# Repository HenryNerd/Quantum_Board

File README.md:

# Quantum Board #
A nice 65% or 95%ish keyboard. It using kailh chocs for great performance while being very small.

## Layout 

## Board Screenshots

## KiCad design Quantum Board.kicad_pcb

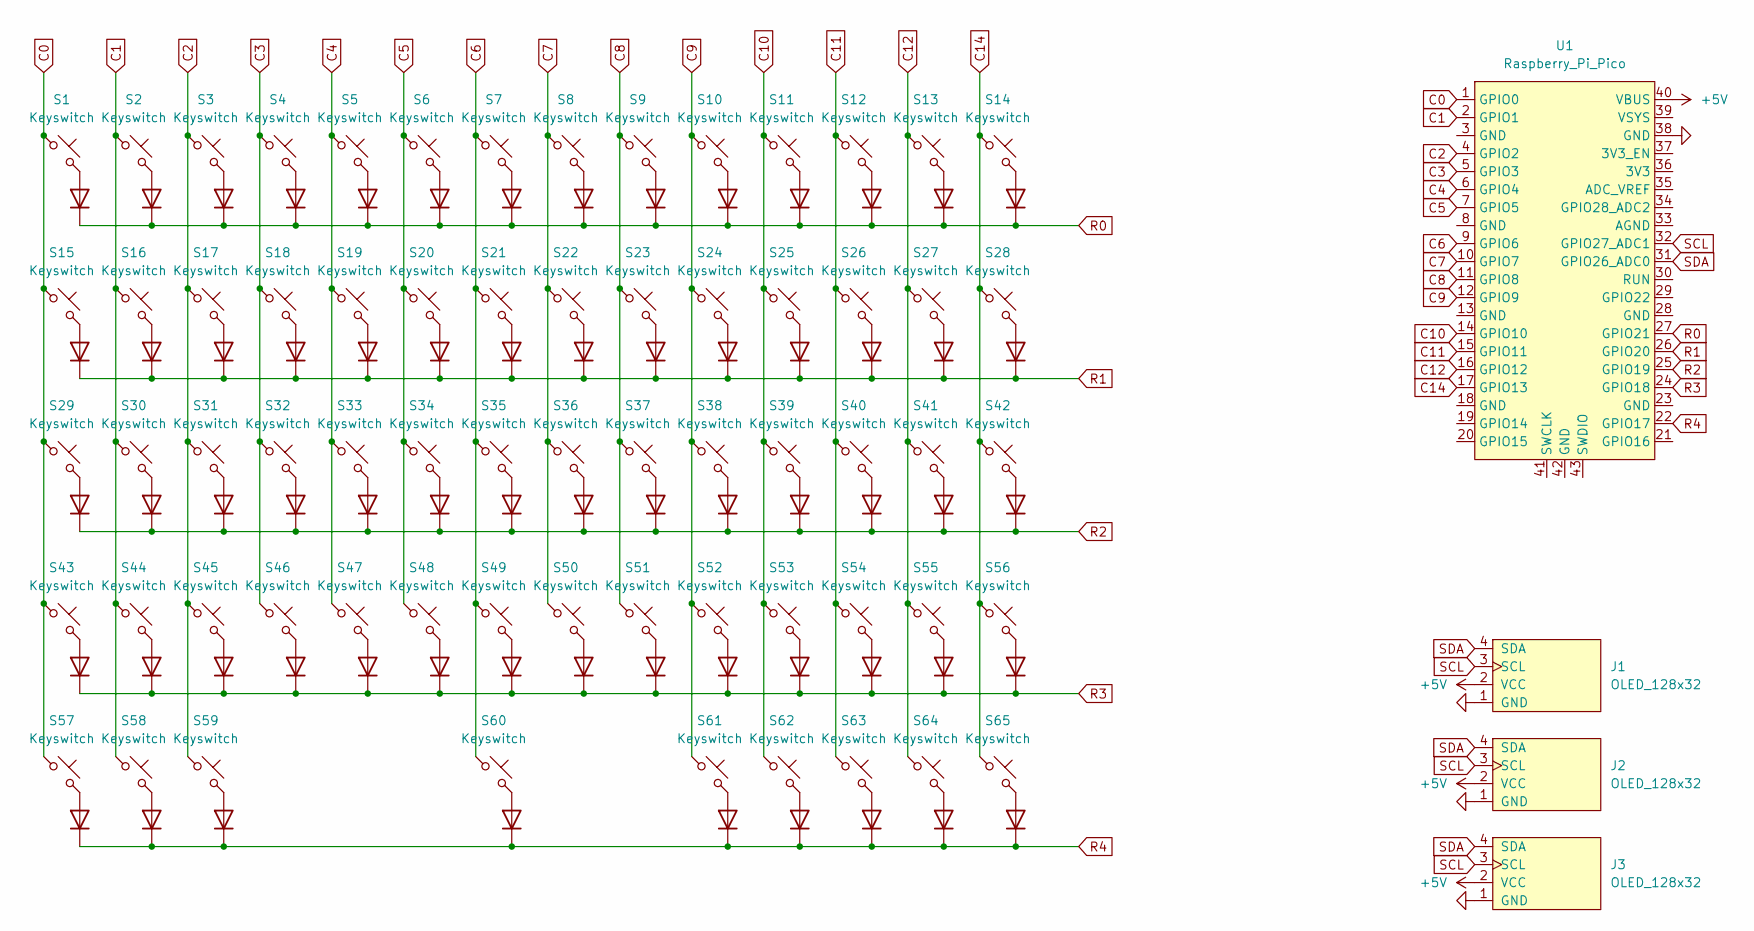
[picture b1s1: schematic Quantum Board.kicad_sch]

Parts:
D1, D2, D3, D4, D5, D6, D7, D8, D9, D10, D11, D12, D13, D14, D15, D16, D17, D18, D19, D20, D21, D22, D23, D24, D25, D26, D27, D28, D29, D30, D31, D32, D33, D34, D35, D36, D37, D38, D39, D40, D41, D42, D43, D44, D45, D46, D47, D48, D49, D50, D51, D52, D53, D54, D55, D56, D57, D58, D59, D60, D61, D62, D63, D64, D65: Diode; Diode_DO-35
J1, J2, J3: OLED_128x32
S1, S14, S15, S28, S29, S42, S43, S56, S57, S58, S59, S62: Keyswitch; Choc_V1_1.50u
S2, S3, S4, S5, S6, S7, S8, S9, S10, S11, S12, S13, S16, S17, S18, S19, S20, S21, S22, S23, S24, S25, S26, S27, S30, S31, S32, S33, S34, S35, S36, S37, S38, S39, S40, S41, S44, S45, S46, S47, S48, S49, S50, S51, S52, S53, S54, S55, S61, S63, S64, S65: Keyswitch; Choc_V1_1.00u
S60: Keyswitch; Choc_V1_5.50u
U1: Raspberry_Pi_Pico

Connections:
+5V: J1.2 (VCC), J2.2 (VCC), J3.2 (VCC), U1.40 (VBUS)
C0: S1.1, S15.1, S29.1, S43.1, S57.1, U1.1 (GPIO0)
C1: S2.1, S16.1, S30.1, S44.1, S58.1, U1.2 (GPIO1)
C2: S3.1, S17.1, S31.1, S45.1, S59.1, U1.4 (GPIO2)
C3: S4.1, S18.1, S32.1, S46.1, U1.5 (GPIO3)
C4: S5.1, S19.1, S33.1, S47.1, U1.6 (GPIO4)
C5: S6.1, S20.1, S34.1, S48.1, U1.7 (GPIO5)
C6: S7.1, S21.1, S35.1, S49.1, S60.1, U1.9 (GPIO6)
C7: S8.1, S22.1, S36.1, S50.1, U1.10 (GPIO7)
C8: S9.1, S23.1, S37.1, S51.1, U1.11 (GPIO8)
C9: S10.1, S24.1, S38.1, S52.1, S61.1, U1.12 (GPIO9); also elsewhere on the board
C10: S11.1, S25.1, S39.1, S53.1, S62.1, U1.14 (GPIO10); also elsewhere on the board
C11: S12.1, S26.1, S40.1, S54.1, S63.1, U1.15 (GPIO11); also elsewhere on the board
C12: S13.1, S27.1, S41.1, S55.1, S64.1, U1.16 (GPIO12); also elsewhere on the board
C14: S14.1, S28.1, S42.1, S56.1, S65.1, U1.17 (GPIO13); also elsewhere on the board
GND: J1.1 (GND), J2.1 (GND), J3.1 (GND), U1.38 (GND)
unnamed: D1.2 (A), S1.2
unnamed: D2.2 (A), S2.2
unnamed: D3.2 (A), S3.2
unnamed: D4.2 (A), S4.2
unnamed: D5.2 (A), S5.2
unnamed: D6.2 (A), S6.2
unnamed: D7.2 (A), S7.2
unnamed: D8.2 (A), S8.2
unnamed: D9.2 (A), S9.2
unnamed: D10.2 (A), S10.2
unnamed: D11.2 (A), S11.2
unnamed: D12.2 (A), S12.2
unnamed: D13.2 (A), S13.2
unnamed: D14.2 (A), S14.2
unnamed: D15.2 (A), S15.2
unnamed: D16.2 (A), S16.2
unnamed: D17.2 (A), S17.2
unnamed: D18.2 (A), S18.2
unnamed: D19.2 (A), S19.2
unnamed: D20.2 (A), S20.2
unnamed: D21.2 (A), S21.2
unnamed: D22.2 (A), S22.2
unnamed: D23.2 (A), S23.2
unnamed: D24.2 (A), S24.2
unnamed: D25.2 (A), S25.2
unnamed: D26.2 (A), S26.2
unnamed: D27.2 (A), S27.2
unnamed: D28.2 (A), S28.2
unnamed: D29.2 (A), S29.2
unnamed: D30.2 (A), S30.2
unnamed: D31.2 (A), S31.2
unnamed: D32.2 (A), S32.2
unnamed: D33.2 (A), S33.2
unnamed: D34.2 (A), S34.2
unnamed: D35.2 (A), S35.2
unnamed: D36.2 (A), S36.2
unnamed: D37.2 (A), S37.2
unnamed: D38.2 (A), S38.2
unnamed: D39.2 (A), S39.2
unnamed: D40.2 (A), S40.2
unnamed: D41.2 (A), S41.2
unnamed: D42.2 (A), S42.2
unnamed: D43.2 (A), S43.2
unnamed: D44.2 (A), S44.2
unnamed: D45.2 (A), S45.2
unnamed: D46.2 (A), S46.2
unnamed: D47.2 (A), S47.2
unnamed: D48.2 (A), S48.2
unnamed: D49.2 (A), S49.2
unnamed: D50.2 (A), S50.2
unnamed: D51.2 (A), S51.2
unnamed: D52.2 (A), S52.2
unnamed: D53.2 (A), S53.2
unnamed: D54.2 (A), S54.2
unnamed: D55.2 (A), S55.2
unnamed: D56.2 (A), S56.2
unnamed: D57.2 (A), S57.2
unnamed: D58.2 (A), S58.2
unnamed: D59.2 (A), S59.2
unnamed 75: D60.2 (A), S61.2; also elsewhere on the board
unnamed: D61.2 (A), S62.2
unnamed: D62.2 (A), S63.2
unnamed: D63.2 (A), S60.2
unnamed: D64.2 (A), S64.2
unnamed: D65.2 (A), S65.2
R0: D1.1 (K), D2.1 (K), D3.1 (K), D4.1 (K), D5.1 (K), D6.1 (K), D7.1 (K), D8.1 (K), D9.1 (K), D10.1 (K), D11.1 (K), D12.1 (K), D13.1 (K), D14.1 (K), U1.27 (GPIO21)
R1: D15.1 (K), D16.1 (K), D17.1 (K), D18.1 (K), D19.1 (K), D20.1 (K), D21.1 (K), D22.1 (K), D23.1 (K), D24.1 (K), D25.1 (K), D26.1 (K), D27.1 (K), D28.1 (K), U1.26 (GPIO20)
R2: D29.1 (K), D30.1 (K), D31.1 (K), D32.1 (K), D33.1 (K), D34.1 (K), D35.1 (K), D36.1 (K), D37.1 (K), D38.1 (K), D39.1 (K), D40.1 (K), D41.1 (K), D42.1 (K), U1.25 (GPIO19)
R3: D43.1 (K), D44.1 (K), D45.1 (K), D46.1 (K), D47.1 (K), D48.1 (K), D49.1 (K), D50.1 (K), D51.1 (K), D52.1 (K), D53.1 (K), D54.1 (K), D55.1 (K), D56.1 (K), U1.24 (GPIO18)
R4: D57.1 (K), D58.1 (K), D59.1 (K), D60.1 (K), D61.1 (K), D62.1 (K), D63.1 (K), D64.1 (K), D65.1 (K), U1.22 (GPIO17); also elsewhere on the board
SCL: J1.3 (SCL), J2.3 (SCL), J3.3 (SCL), U1.32 (GPIO27_ADC1)
SDA: J1.4 (SDA), J2.4 (SDA), J3.4 (SDA), U1.31 (GPIO26_ADC0)

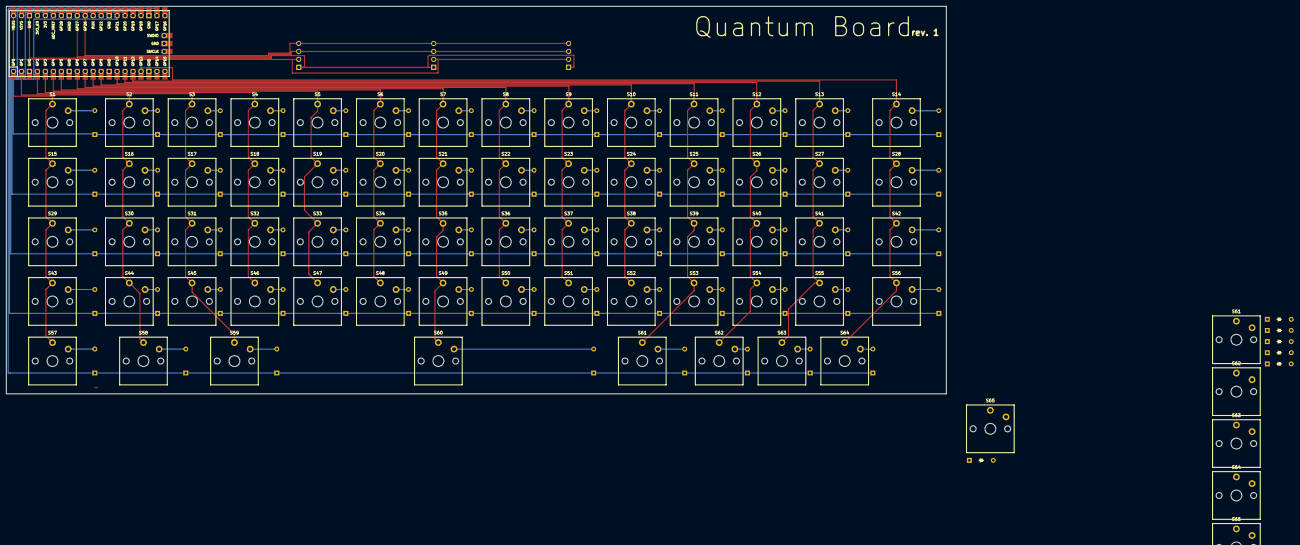
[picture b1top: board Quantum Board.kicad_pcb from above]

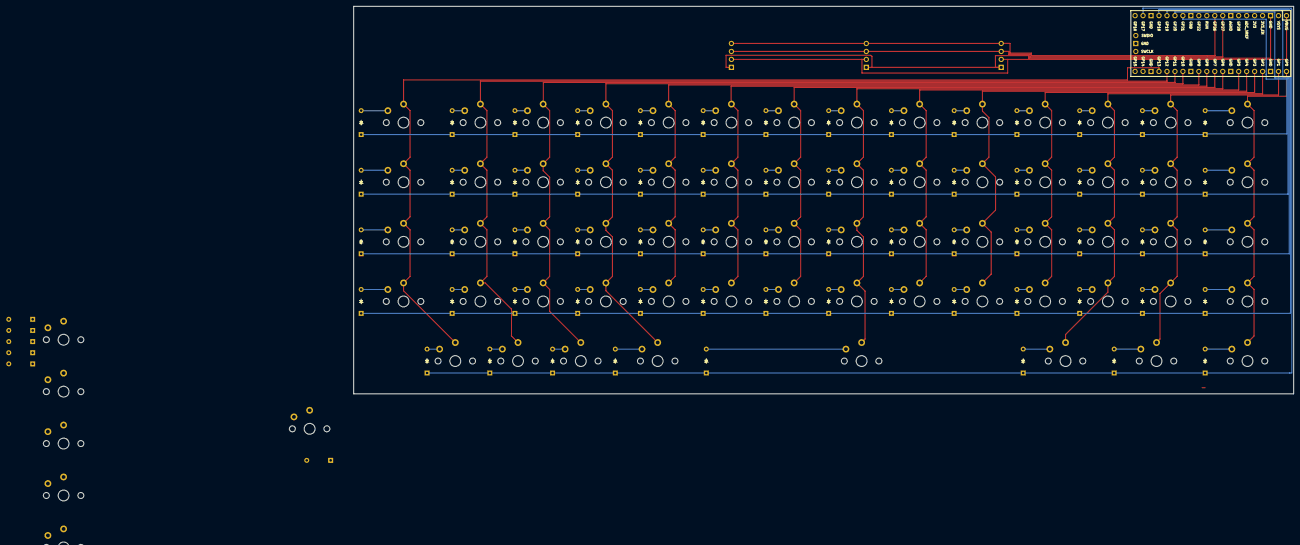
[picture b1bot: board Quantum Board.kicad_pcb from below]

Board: 2 copper layers, 299.6 x 123.5 mm, 144 parts (64 on the bottom side), 92 nets.

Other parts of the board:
D60#2, D67, D68, D69, D70: Diode; Diode_DO-35
S61#2, S65#2: Keyswitch; Choc_V1_1.50u
S62#2, S63#2, S64#2: Keyswitch; Choc_V1_1.00u

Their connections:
C9: S65#2.1; also elsewhere on the board
C10: S61#2.1; also elsewhere on the board
C11: S62#2.1; also elsewhere on the board
C12: S63#2.1; also elsewhere on the board
C14: S64#2.1; also elsewhere on the board
unnamed 75: D60#2.2 (A), S65#2.2; also elsewhere on the board
unnamed: D67.2 (A), S61#2.2
unnamed: D68.2 (A), S62#2.2
unnamed: D69.2 (A), S63#2.2
unnamed: D70.2 (A), S64#2.2
R4: D60#2.1 (K), D67.1 (K), D68.1 (K), D69.1 (K), D70.1 (K); also elsewhere on the board

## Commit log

2024-08-30 Quantum Board Part 1
2024-08-31 Quantum Board Part 2
2024-08-31 Quantum Board Part 3
2024-08-31 Quantum Board Part 4
2024-08-31 Quantum Board Part 5
2024-08-31 Quantum Board Part 6
2024-08-31 Quantum Board Part 7
